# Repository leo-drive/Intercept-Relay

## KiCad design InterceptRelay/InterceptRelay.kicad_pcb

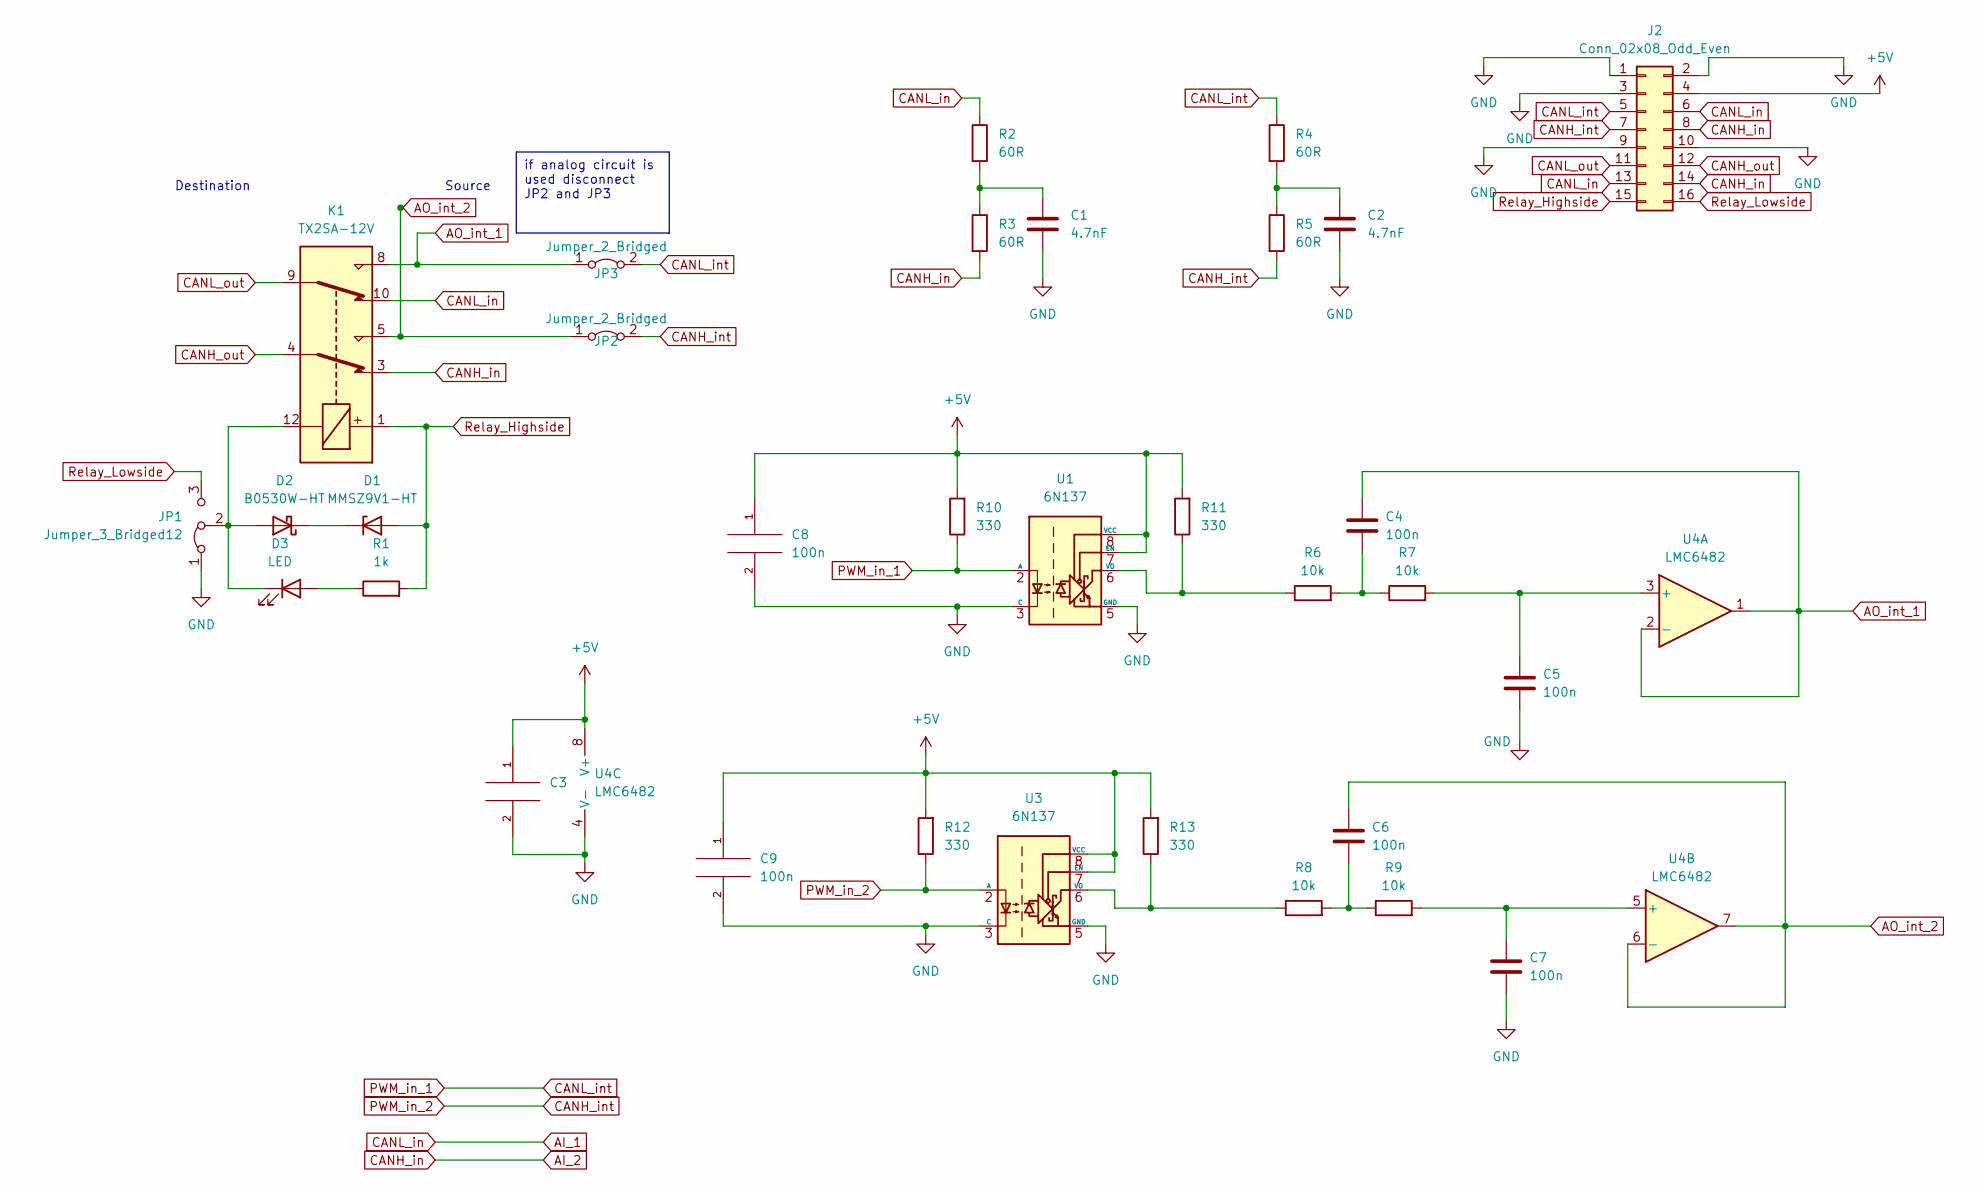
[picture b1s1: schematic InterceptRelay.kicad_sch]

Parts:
C1, C2: 4.7nF; C_0603_1608Metric
C3, C4, C5, C6, C7, C8, C9: 100n; C_0603_1608Metric
D1: MMSZ9V1-HT; D_SOD-123
D2: B0530W-HT; D_SOD-123
D3: LED; LED_0603_1608Metric
J2: Conn_02x08_Odd_Even; S16B-PADSS-1
JP1: Jumper_3_Bridged12; SolderJumper-3_P1.3mm_Bridged12_RoundedPad1.0x1.5mm
JP2, JP3: Jumper_2_Bridged; SolderJumper-2_P1.3mm_Bridged_RoundedPad1.0x1.5mm
K1: TX2SA-12V; Relay_DPDT_Kemet_EE2_NU
R1: 1k; R_0603_1608Metric
R2, R3, R4, R5: 60R; R_0603_1608Metric
R6, R7, R8, R9: 10k; R_0603_1608Metric
R10, R11, R12, R13: 330; R_0603_1608Metric
U1, U3: 6N137; SMDIP-8_W9.53mm
U4: LMC6482; SOIC-8_3.9x4.9mm_P1.27mm

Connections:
+5V: C3.1, C8.1, C9.1, J2.4, R10.2, R11.2, R12.2, R13.2, U1.7 (EN), U1.8 (VCC), U3.7 (EN), U3.8 (VCC), U4.8 (V+)
AI_1: J2.6, J2.13, K1.10, R2.1
AI_2: J2.8, J2.14, K1.3, R3.2
AO_int_1: C4.1, JP3.1 (A), K1.8, U4.1, U4.2 (-)
AO_int_2: C6.1, JP2.1 (A), K1.5, U4.6 (-), U4.7
CANH_int: J2.7, JP2.2 (B), R5.2, R12.1, U3.2 (A)
CANH_out: J2.12, K1.4
CANL_int: J2.5, JP3.2 (B), R4.1, R10.1, U1.2 (A)
CANL_out: J2.11, K1.9
GND: C1.2, C2.2, C3.2, C5.2, C7.2, C8.2, C9.2, J2.1, J2.2, J2.3, J2.9, J2.10, JP1.1 (A), U1.3 (C), U1.5 (GND), U3.3 (C), U3.5 (GND), U4.4 (V-)
unnamed: C1.1, R2.2, R3.1
unnamed: C2.1, R4.2, R5.1
unnamed: C4.2, R6.2, R7.1
unnamed: C6.2, R8.2, R9.1
unnamed: D1.1 (K), D2.1 (K)
unnamed: D2.2 (A), D3.1 (K), JP1.2 (C), K1.12
unnamed: D3.2 (A), R1.1
unnamed: R6.1, R11.1, U1.6 (VO)
unnamed: R8.1, R13.1, U3.6 (VO)
unnamed: C5.1, R7.2, U4.3 (+)
unnamed: C7.1, R9.2, U4.5 (+)
Relay_Highside: D1.2 (A), J2.15, K1.1, R1.2
Relay_Lowside: J2.16, JP1.3 (B)

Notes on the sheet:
if analog circuit is used disconnect JP2 and JP3
Source
Destination

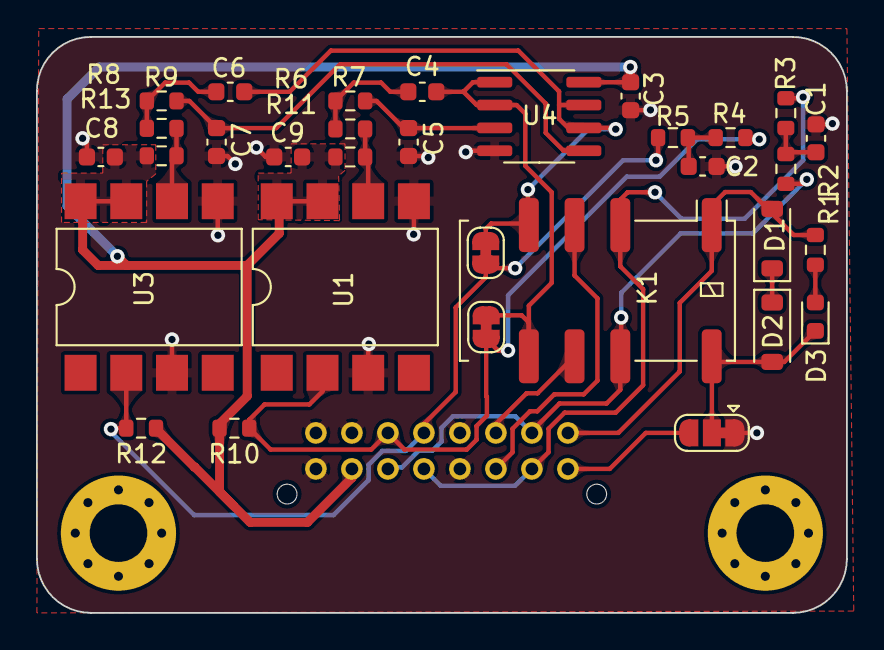
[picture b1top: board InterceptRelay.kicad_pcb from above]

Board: 2 copper layers, 45.0 x 32.0 mm, 33 parts (0 on the bottom side), 23 nets.

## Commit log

2024-02-13 add files
